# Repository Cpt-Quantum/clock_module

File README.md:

# Clock Module
This repo contains the schematic and PCB design for a clock module that features both a variable frequency clock (from a 555 timer) and a single step mode. The schematic is based very closely on Ben Eater's design (https://eater.net/8bit/clock), and will be used alongside his breadboard 6502 project.

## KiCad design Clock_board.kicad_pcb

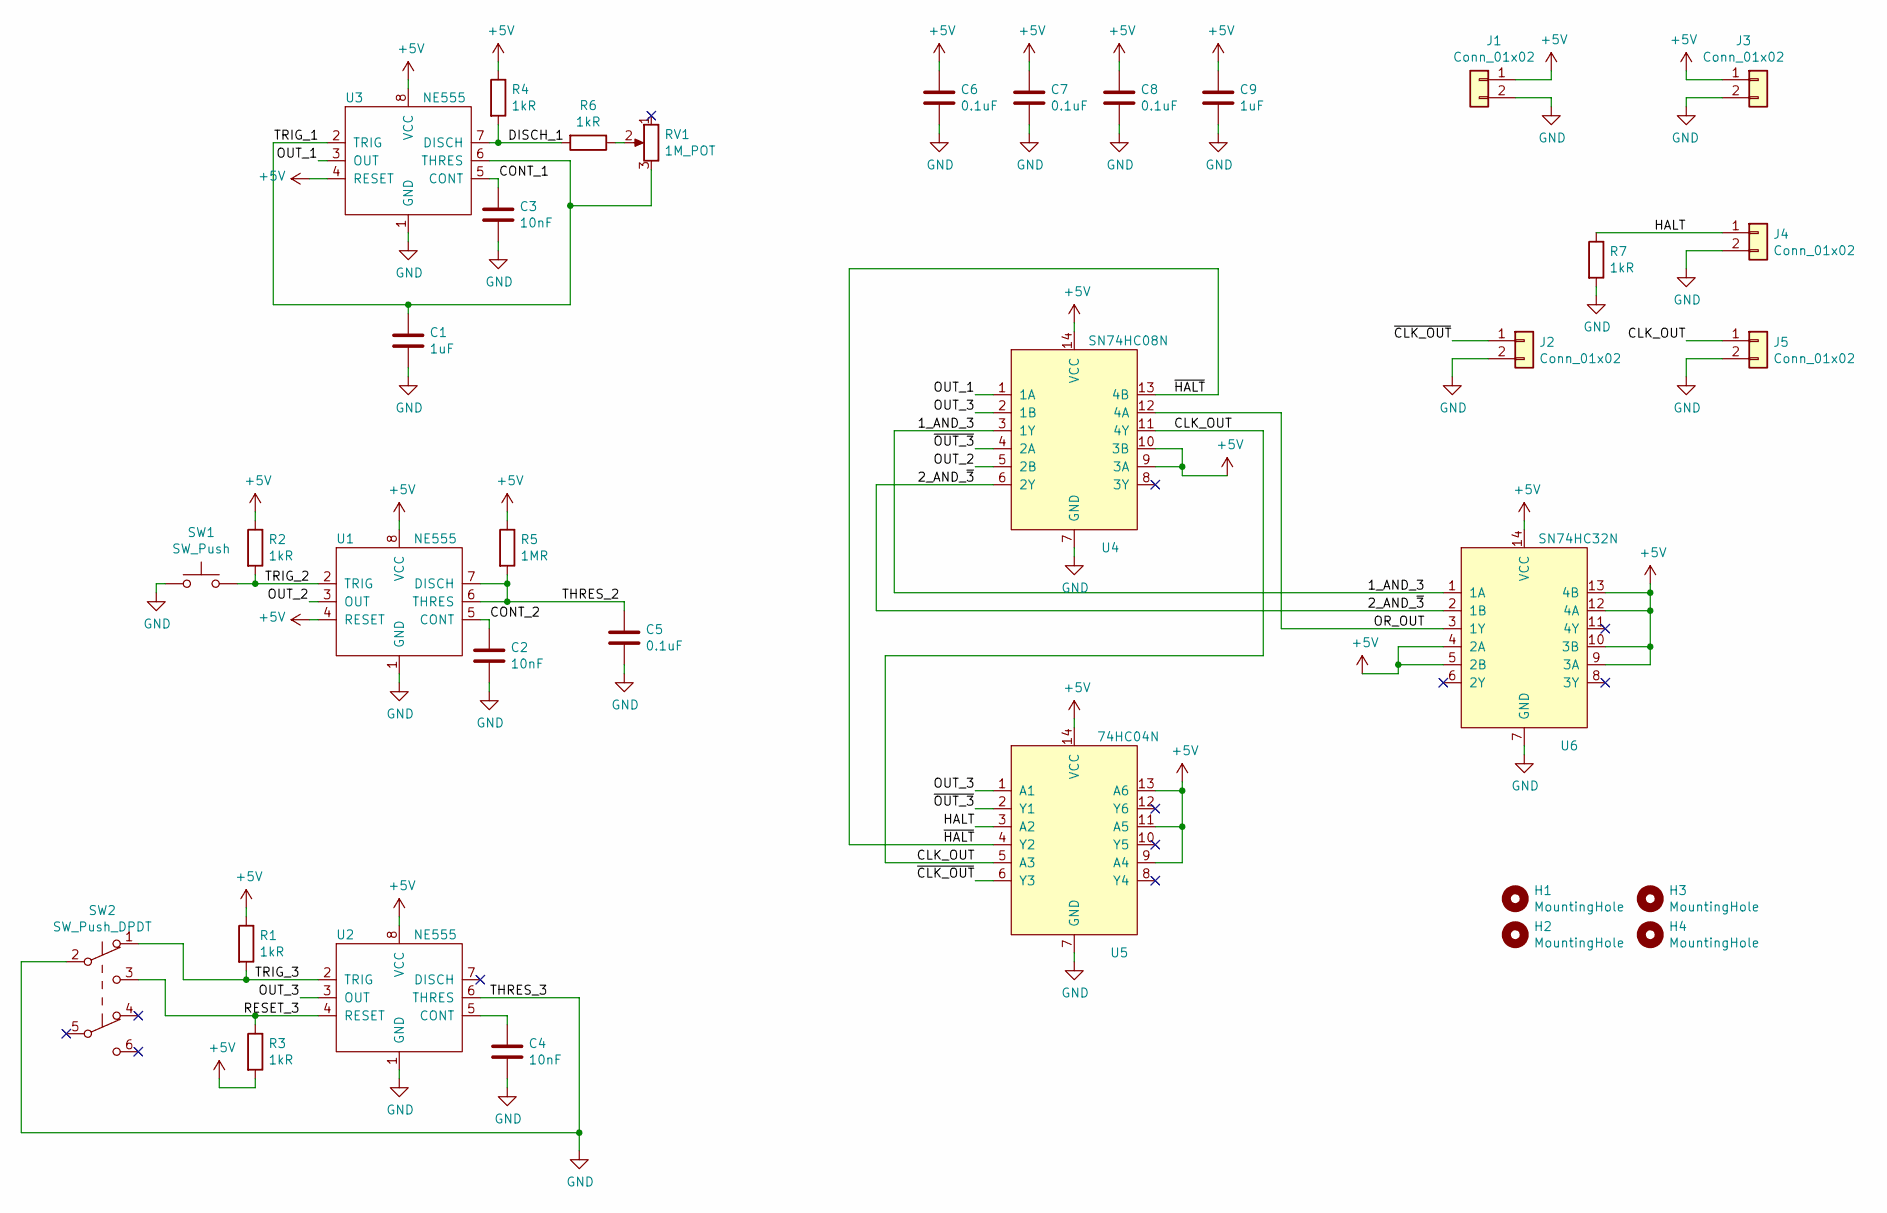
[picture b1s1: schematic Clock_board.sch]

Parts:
C1, C9: 1uF; C_Disc_D4.7mm_W2.5mm_P5.00mm; Mfr Part # CD1H105MC9BEF4E000
C2, C3, C4: 10nF; C_Disc_D4.7mm_W2.5mm_P5.00mm; Mfr Part # CD1H103KC94ER1D000
C5, C6, C7, C8: 0.1uF; C_Disc_D4.7mm_W2.5mm_P5.00mm; Mfr Part # CD1H104MC9BEF4D000
H1, H2, H3, H4: MountingHole; MountingHole_2.5mm
J1, J2, J3, J4, J5: Conn_01x02; PinHeader_1x02_P2.54mm_Vertical
R1, R2, R3, R4, R6, R7: 1kR; R_Axial_DIN0207_L6.3mm_D2.5mm_P7.62mm_Horizontal
R5: 1MR; R_Axial_DIN0207_L6.3mm_D2.5mm_P7.62mm_Horizontal
RV1: 1M_POT; Potentiometer_Runtron_RM-065_Vertical
SW1: SW_Push; SW_PUSH_6mm_H5mm
SW2: SW_Push_DPDT; DPDT-Latching-PB12E06371; Mfr Part # PB12E06371
U1, U2, U3: NE555; DIP-8_W7.62mm; Mfr Part # NE555N
U4: SN74HC08N; DIP-14_W7.62mm; Mfr Part # SN74HC08N
U5: 74HC04N; DIP-14_W7.62mm; Mfr Part # 74HC04N
U6: SN74HC32N; DIP-14_W7.62mm; Mfr Part # SN74HC32N

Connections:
+5V: C6.1, C7.1, C8.1, C9.1, J1.1, J3.1, R1.1, R2.1, R3.2, R4.1, R5.1, U1.4 (RESET), U1.8 (VCC), U2.8 (VCC), U3.4 (RESET), U3.8 (VCC), U4.9 (3A), U4.10 (3B), U4.14 (VCC), U5.9 (A4), U5.11 (A5), U5.13 (A6), U5.14 (VCC), U6.4 (2A), U6.5 (2B), U6.9 (3A), U6.10 (3B), U6.12 (4A), U6.13 (4B), U6.14 (VCC)
/1_AND_3: U4.3 (1Y), U6.1 (1A)
/2_AND_~3: U4.6 (2Y), U6.2 (1B)
/CLK_OUT: J5.1, U4.11 (4Y), U5.5 (A3)
/CONT_1: C3.1, U3.5 (CONT)
/CONT_2: C2.1, U1.5 (CONT)
/DISCH_1: R4.2, R6.2, U3.7 (DISCH)
/HALT: J4.1, R7.1, U5.3 (A2)
/OR_OUT: U4.12 (4A), U6.3 (1Y)
/OUT_1: U3.3 (OUT), U4.1 (1A)
/OUT_2: U1.3 (OUT), U4.5 (2B)
/OUT_3: U2.3 (OUT), U4.2 (1B), U5.1 (A1)
/RESET_3: R3.1, SW2.3 (C), U2.4 (RESET)
/THRES_2: C5.1, R5.2, U1.6 (THRES), U1.7 (DISCH)
/TRIG_1: C1.1, RV1.3, U3.2 (TRIG), U3.6 (THRES)
/TRIG_2: R2.2, SW1.2, U1.2 (TRIG)
/TRIG_3: R1.2, SW2.1 (A), U2.2 (TRIG)
/~CLK_OUT: J2.1, U5.6 (Y3)
/~HALT: U4.13 (4B), U5.4 (Y2)
/~OUT_3: U4.4 (2A), U5.2 (Y1)
GND: C1.2, C2.2, C3.2, C4.2, C5.2, C6.2, C7.2, C8.2, C9.2, J1.2, J2.2, J3.2, J4.2, J5.2, R7.2, SW1.1, SW2.2 (B), U1.1 (GND), U2.1 (GND), U2.6 (THRES), U3.1 (GND), U4.7 (GND), U5.7 (GND), U6.7 (GND)
unnamed: C4.1, U2.5 (CONT)
unnamed: R6.1, RV1.2

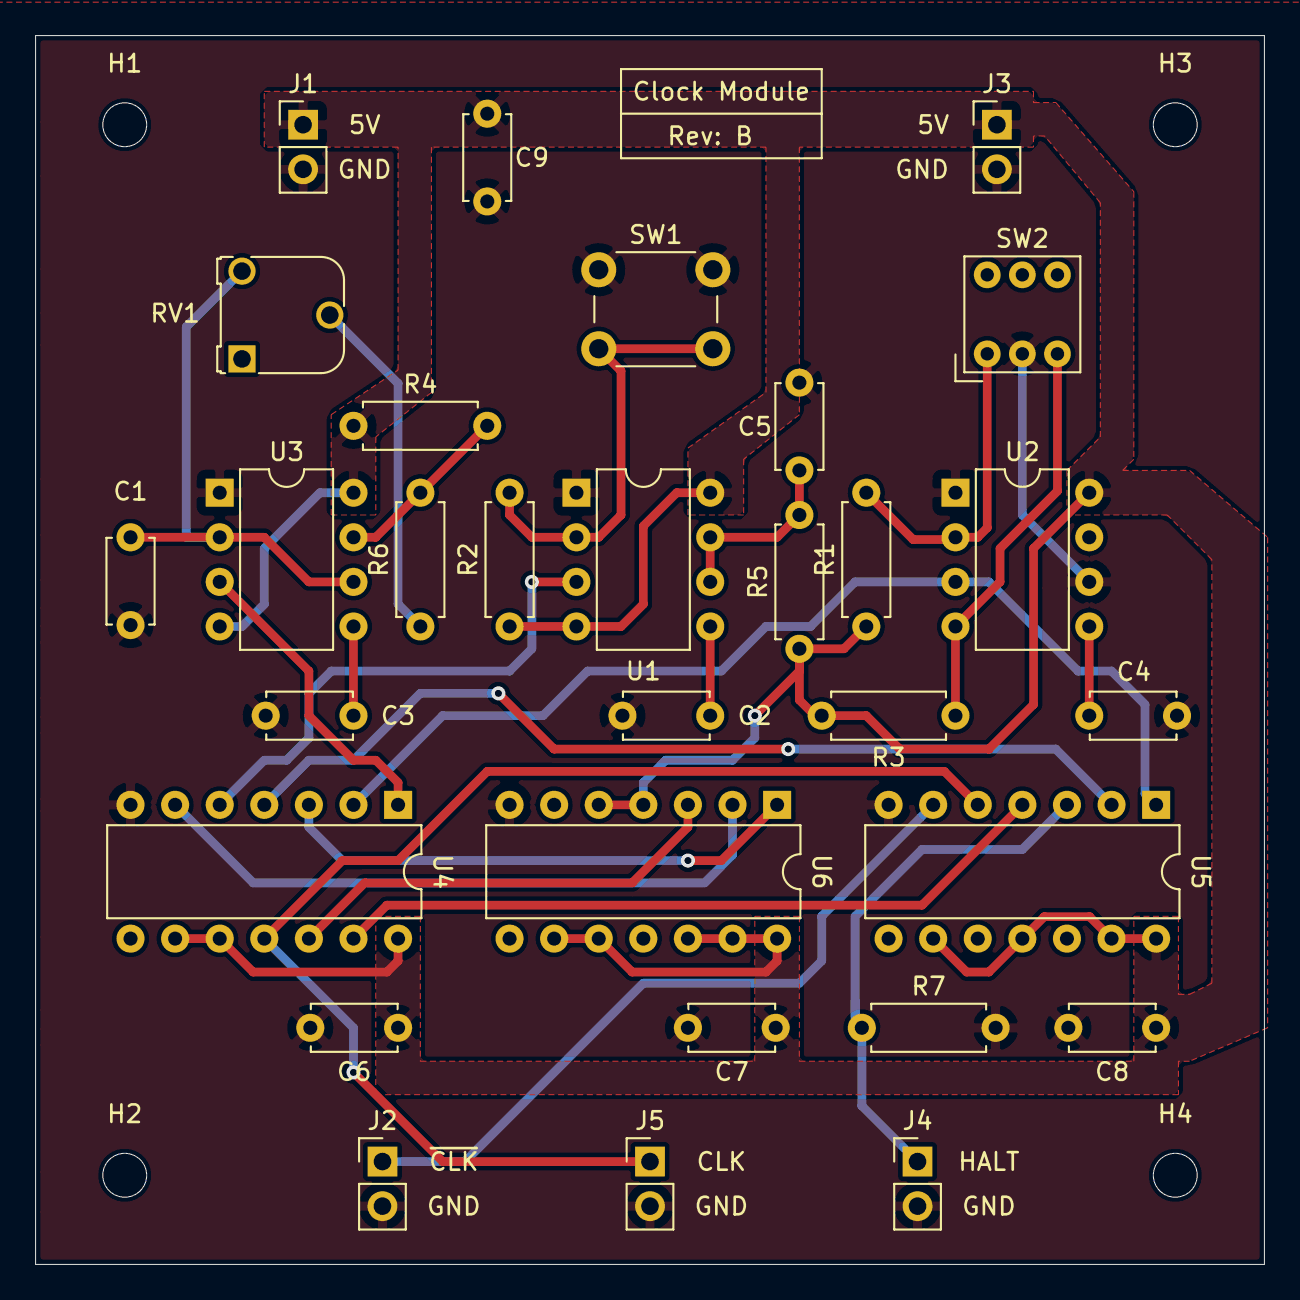
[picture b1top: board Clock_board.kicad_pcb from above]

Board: 2 copper layers, 70.0 x 70.0 mm, 34 parts (0 on the bottom side), 23 nets.

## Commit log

2020-10-25 Added .gitignore file
2020-10-25 Initial Rev A files commit
2020-11-07 Fixed the resistor footprints and changed revision to B
